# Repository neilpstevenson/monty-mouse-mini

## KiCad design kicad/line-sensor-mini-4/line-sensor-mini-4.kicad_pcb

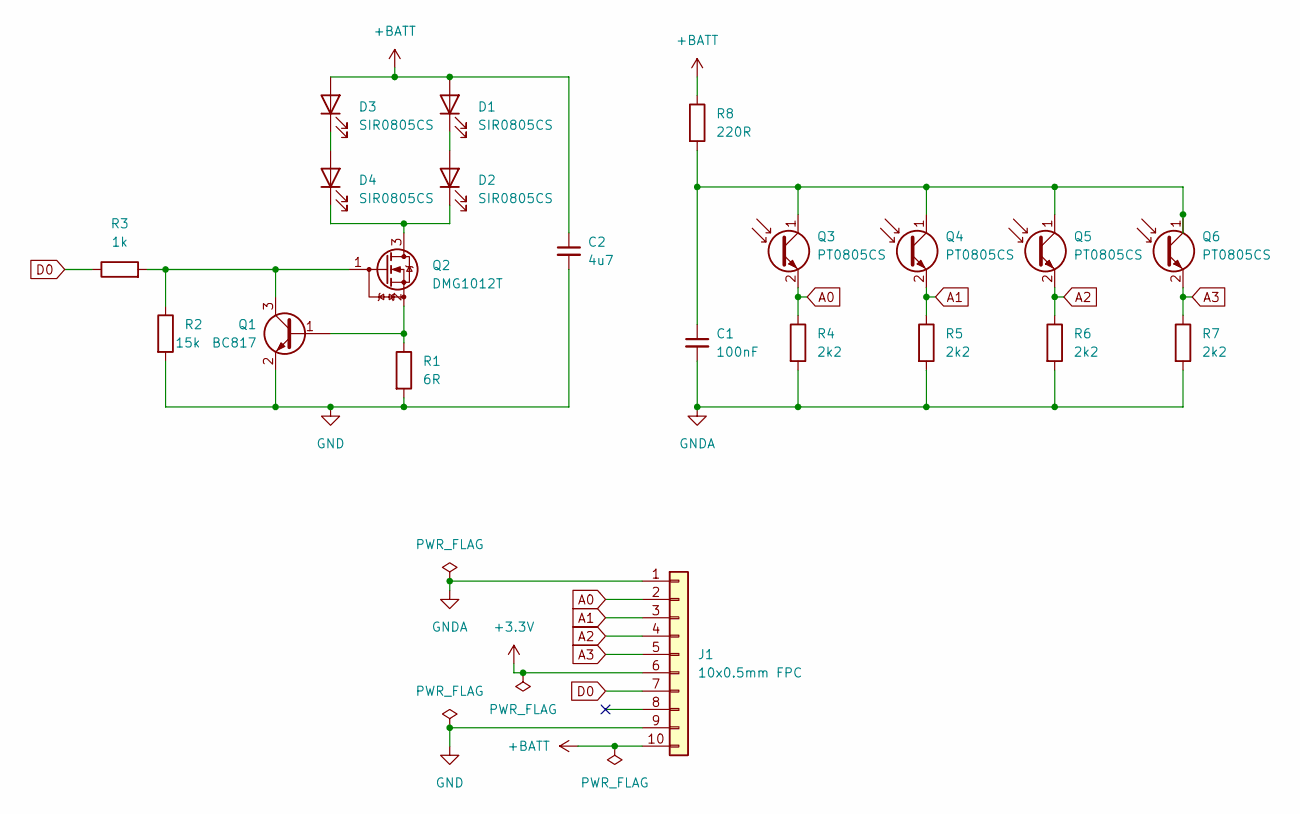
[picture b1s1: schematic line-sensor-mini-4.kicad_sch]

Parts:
C1: 100nF; C_0805_2012Metric
C2: 4u7; C_0805_2012Metric
D1, D2, D3, D4: SIR0805CS; LED_0805_2012Metric_Pad1.15x1.40mm_HandSolder
J1: 10x0.5mm FPC; TE_1-1734839-0_1x10-1MP_P0.5mm_Horizontal
Q1: BC817; SOT-23
Q2: DMG1012T; SOT-323_SC-70
Q3, Q4, Q5, Q6: PT0805CS; LED_0805_2012Metric_Pad1.15x1.40mm_HandSolder
R1: 6R; R_0805_2012Metric
R2: 15k; R_0805_2012Metric
R3: 1k; R_0805_2012Metric
R4, R5, R6, R7: 2k2; R_0805_2012Metric
R8: 220R; R_0805_2012Metric

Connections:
+3.3V: J1.6
+BATT: C2.1, D1.2 (A), D3.2 (A), J1.10, R8.1
A0: J1.2, Q3.2 (E), R4.1
A1: J1.3, Q4.2 (E), R5.1
A2: J1.4, Q5.2 (E), R6.1
A3: J1.5, Q6.2 (E), R7.1
D0: J1.7, R3.1
GND: C2.2, J1.9, Q1.2 (E), R1.2, R2.2
GNDA: C1.2, J1.1, R4.2, R5.2, R6.2, R7.2
unnamed: D1.1 (K), D2.2 (A)
unnamed: D2.1 (K), D4.1 (K), Q2.3 (D)
unnamed: D3.1 (K), D4.2 (A)
unnamed: Q1.1 (B), Q2.2 (S), R1.1
unnamed: Q1.3 (C), Q2.1 (G), R2.1, R3.2
unnamed: C1.1, Q3.1 (C), Q4.1 (C), Q5.1 (C), Q6.1 (C), R8.2

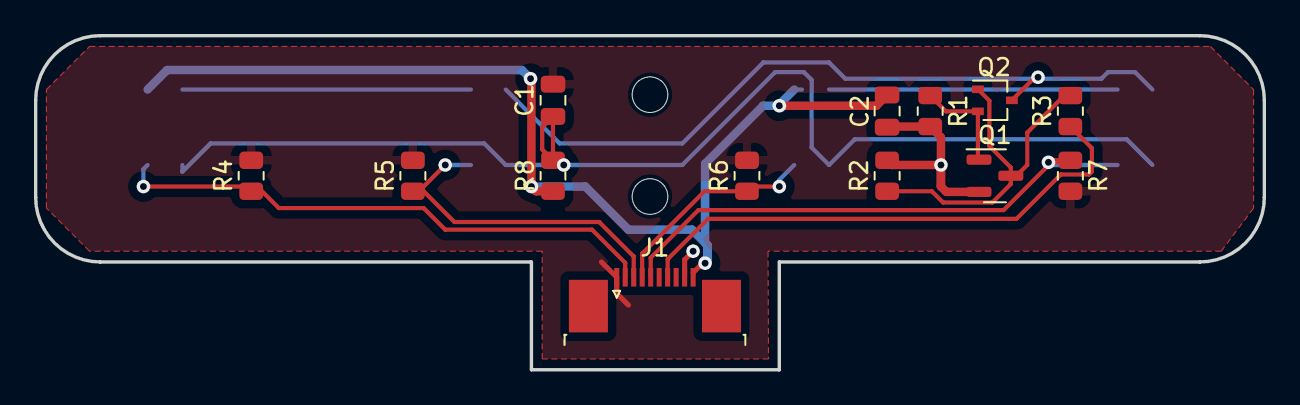
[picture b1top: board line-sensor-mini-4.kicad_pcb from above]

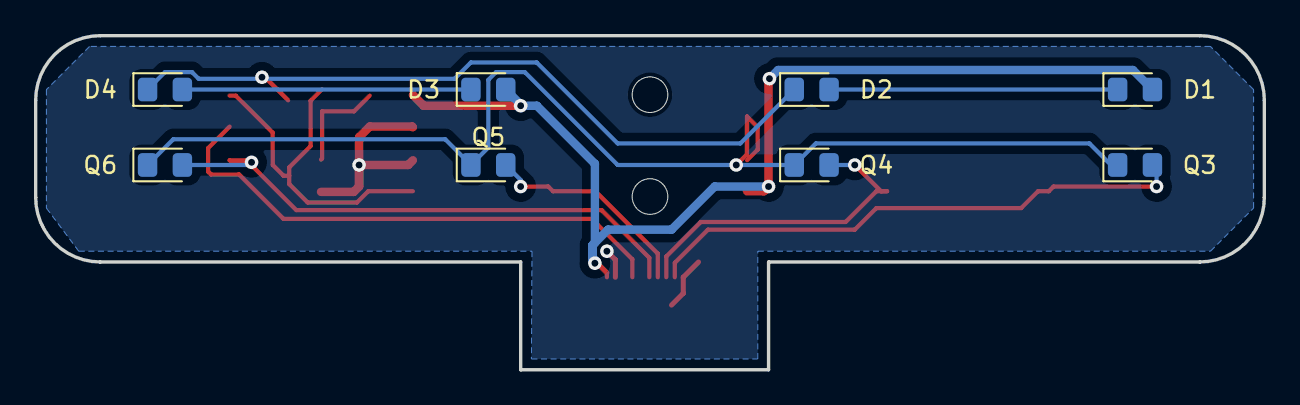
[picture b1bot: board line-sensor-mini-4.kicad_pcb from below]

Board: 2 copper layers, 72.4 x 19.7 mm, 23 parts (8 on the bottom side), 14 nets.

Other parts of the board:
REF-mh: MountingHole_2.1mm
REF-mh#2: MountingHole_2.1mm

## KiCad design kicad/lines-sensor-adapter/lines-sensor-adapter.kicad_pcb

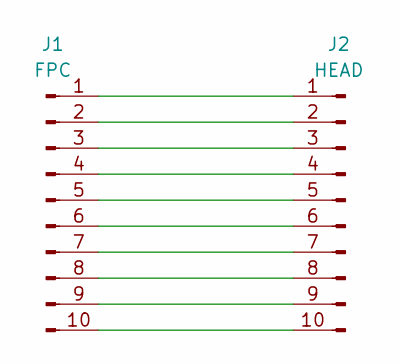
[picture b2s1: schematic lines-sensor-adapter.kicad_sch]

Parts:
J1: FPC; Hirose_FH12-10S-0.5SH_1x10-1MP_P0.50mm_Horizontal
J2: HEAD; PinHeader_1x10_P2.54mm_Vertical

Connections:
unnamed: J1.1, J2.1
unnamed: J1.2, J2.2
unnamed: J1.3, J2.3
unnamed: J1.4, J2.4
unnamed: J1.5, J2.5
unnamed: J1.6, J2.6
unnamed: J1.7, J2.7
unnamed: J1.8, J2.8
unnamed: J1.9, J2.9
unnamed: J1.10, J2.10

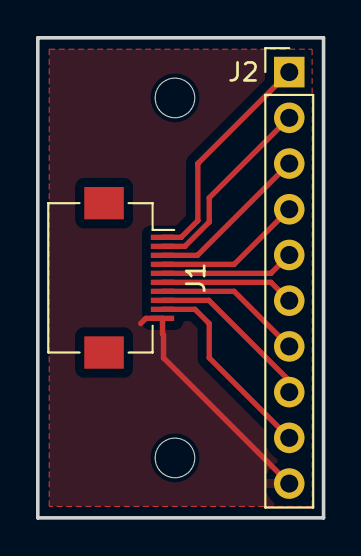
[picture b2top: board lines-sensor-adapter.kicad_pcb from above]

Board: 2 copper layers, 15.9 x 26.7 mm, 4 parts (0 on the bottom side), 10 nets.

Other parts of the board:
REF-mh: MountingHole_2.2mm_M2_DIN965
REF-mh#2: MountingHole_2.2mm_M2_DIN965

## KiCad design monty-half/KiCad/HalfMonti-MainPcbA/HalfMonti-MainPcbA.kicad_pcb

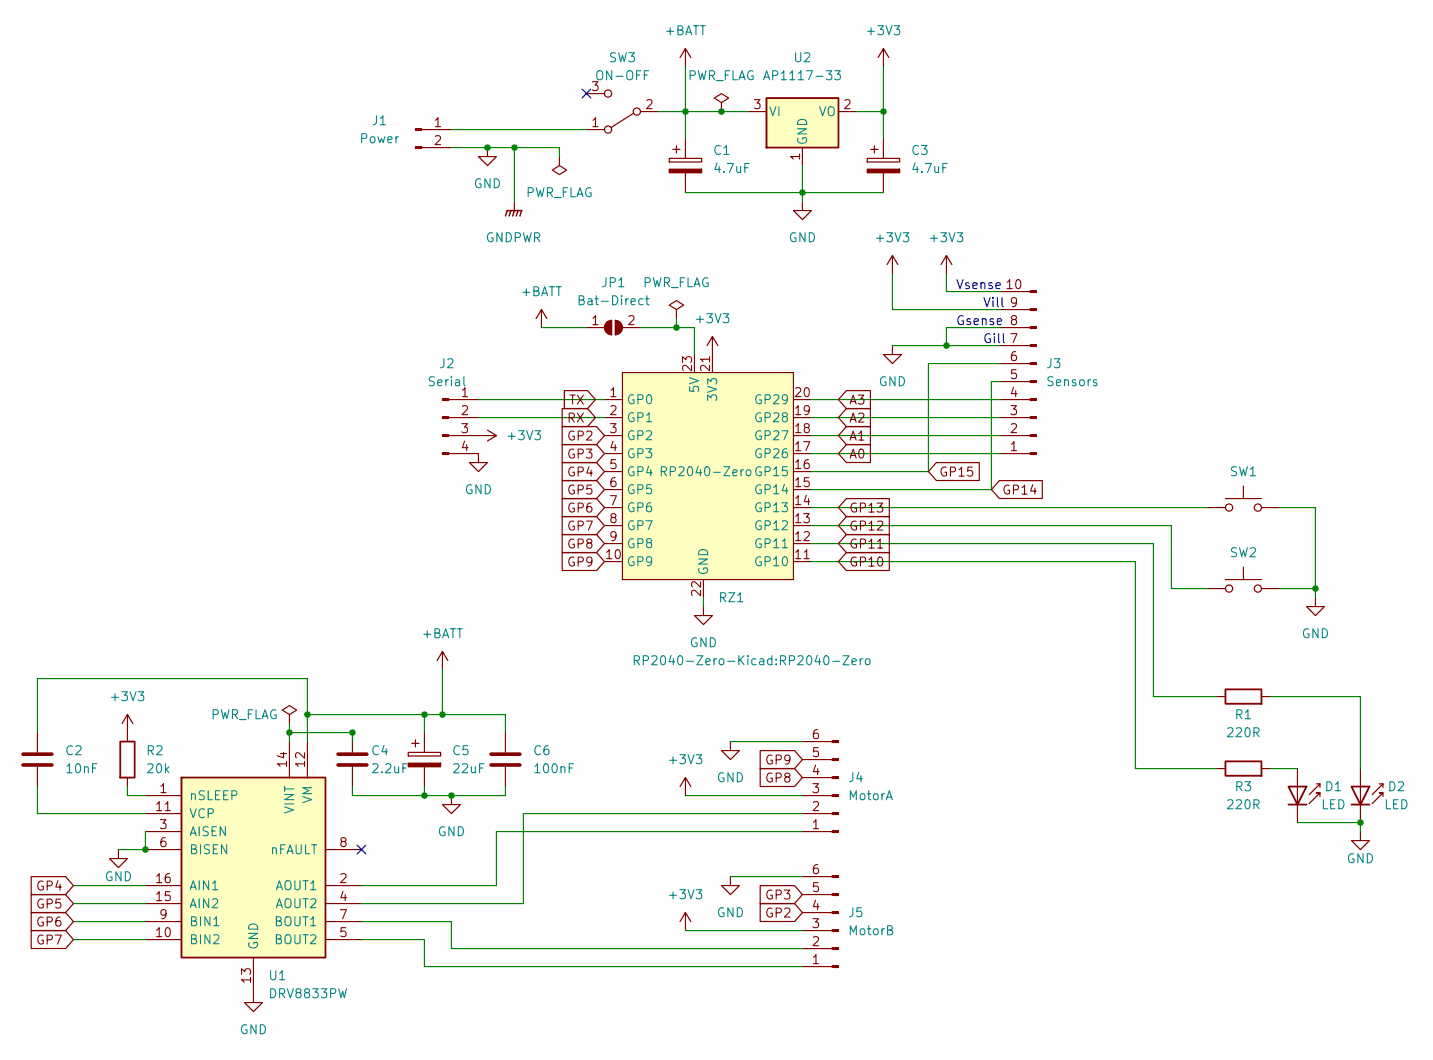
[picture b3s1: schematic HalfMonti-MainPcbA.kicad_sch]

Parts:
C1, C3: 4.7uF; C_0805_2012Metric_Pad1.18x1.45mm_HandSolder
C2: 10nF; C_0805_2012Metric_Pad1.18x1.45mm_HandSolder
C4: 2.2uF; C_0805_2012Metric_Pad1.18x1.45mm_HandSolder
C5: 22uF; CP_Elec_5x3.9
C6: 100nF; C_0805_2012Metric_Pad1.18x1.45mm_HandSolder
D1, D2: LED; LED_1206_3216Metric_Pad1.42x1.75mm_HandSolder
J1: Power; JST_PH_B2B-PH-K_1x02_P2.00mm_Vertical
J2: Serial; PinHeader_1x04_P2.54mm_Vertical
J3: Sensors; PinHeader_1x10_P1.27mm_Vertical
J4: MotorA; PinHeader_1x06_P1.27mm_Vertical
J5: MotorB; PinHeader_1x06_P1.27mm_Vertical
JP1: Bat-Direct; SolderJumper-2_P1.3mm_Open_Pad1.0x1.5mm
R1, R3: 220R; R_0805_2012Metric_Pad1.20x1.40mm_HandSolder
R2: 20k; R_0805_2012Metric_Pad1.20x1.40mm_HandSolder
RZ1: RP2040-Zero
SW1, SW2: SW_Push; SW_SPST_CK_RS282G05A3
SW3: ON-OFF; SW_SPDT_PCM12
U1: DRV8833PW; TSSOP-16_4.4x5mm_P0.65mm
U2: AP1117-33; SOT-223-3_TabPin2

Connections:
+3V3: C3.1, J2.3, J3.9, J3.10, J4.3, J5.3, R2.1, RZ1.21 (3V3), U2.2 (VO)
+BATT: C1.1, C2.1, C5.1, C6.1, JP1.1 (A), SW3.2 (B), U1.12 (VM), U2.3 (VI)
A0: J3.1, RZ1.17 (GP26)
A1: J3.2, RZ1.18 (GP27)
A2: J3.3, RZ1.19 (GP28)
A3: J3.4, RZ1.20 (GP29)
GND: C1.2, C3.2, C4.1, C5.2, C6.2, D1.1 (K), D2.1 (K), J1.2, J2.4, J3.7, J3.8, J4.6, J5.6, RZ1.22 (GND), SW1.2, SW2.2, U1.3 (AISEN), U1.6 (BISEN), U1.13 (GND), U2.1 (GND)
GP2: J5.4, RZ1.3 (GP2)
GP3: J5.5, RZ1.4 (GP3)
GP4: RZ1.5 (GP4), U1.16 (AIN1)
GP5: RZ1.6 (GP5), U1.15 (AIN2)
GP6: RZ1.7 (GP6), U1.9 (BIN1)
GP7: RZ1.8 (GP7), U1.10 (BIN2)
GP8: J4.4, RZ1.9 (GP8)
GP9: J4.5, RZ1.10 (GP9)
GP10: R3.1, RZ1.11 (GP10)
GP11: R1.1, RZ1.12 (GP11)
GP12: RZ1.13 (GP12), SW2.1
GP13: RZ1.14 (GP13), SW1.1
GP14: J3.5, RZ1.15 (GP14)
GP15: J3.6, RZ1.16 (GP15)
unnamed: C2.2, U1.11 (VCP)
unnamed: C4.2, U1.14 (VINT)
unnamed: D1.2 (A), R3.2
unnamed: D2.2 (A), R1.2
unnamed: J1.1, SW3.1 (A)
unnamed: J4.1, U1.2 (AOUT1)
unnamed: J4.2, U1.4 (AOUT2)
unnamed: J5.1, U1.5 (BOUT2)
unnamed: JP1.2 (B), RZ1.23 (5V)
unnamed: R2.2, U1.1 (nSLEEP)
unnamed: J5.2, U1.7 (BOUT1)
RX: J2.2, RZ1.2 (GP1)
TX: J2.1, RZ1.1 (GP0)

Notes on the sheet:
Gsense
Gill
Vsense
Vill

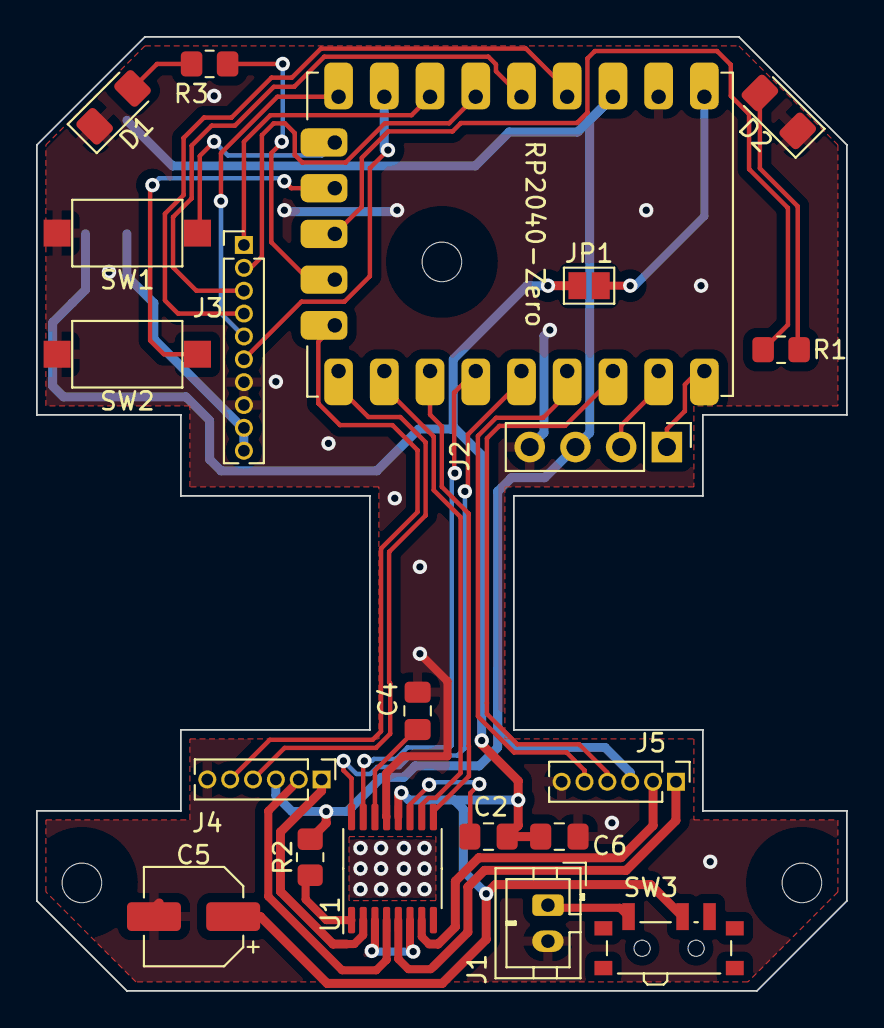
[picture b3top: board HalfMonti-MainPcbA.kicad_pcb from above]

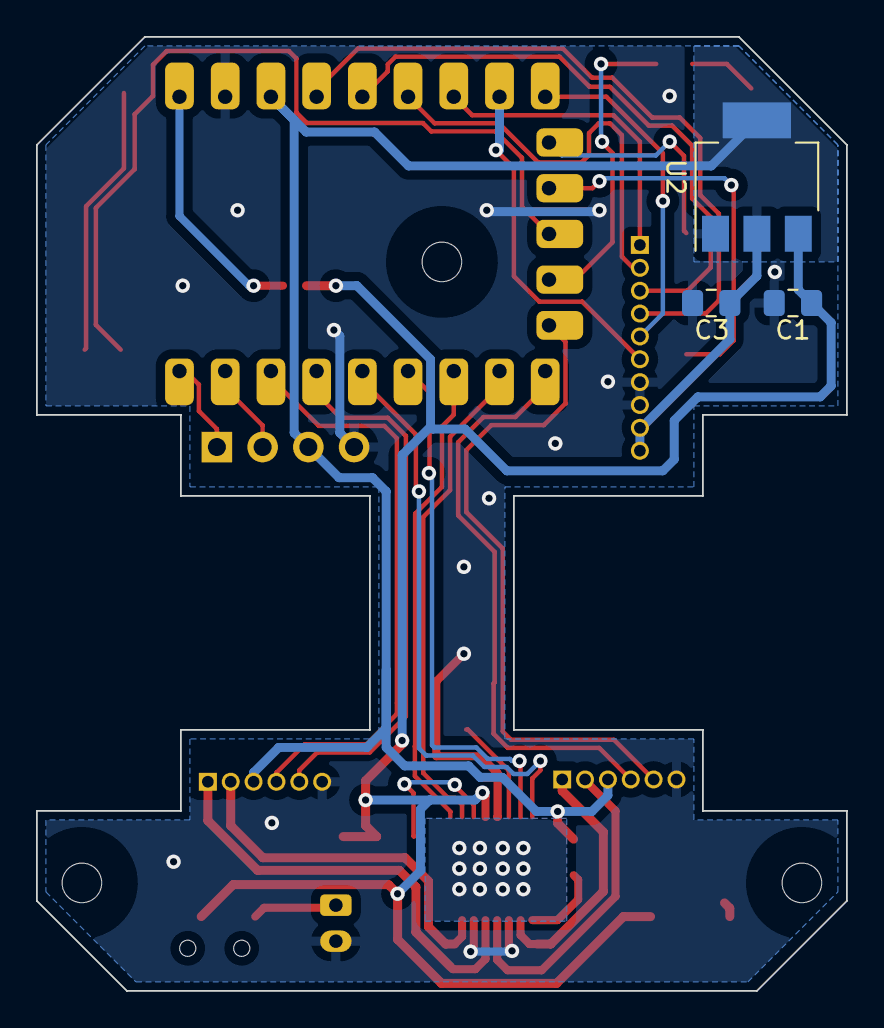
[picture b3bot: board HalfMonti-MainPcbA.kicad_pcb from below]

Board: 2 copper layers, 45.0 x 53.0 mm, 26 parts (4 on the bottom side), 34 nets.

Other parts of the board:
REFH1, REFH2, REFH3: MountingHole_2.2mm_M2

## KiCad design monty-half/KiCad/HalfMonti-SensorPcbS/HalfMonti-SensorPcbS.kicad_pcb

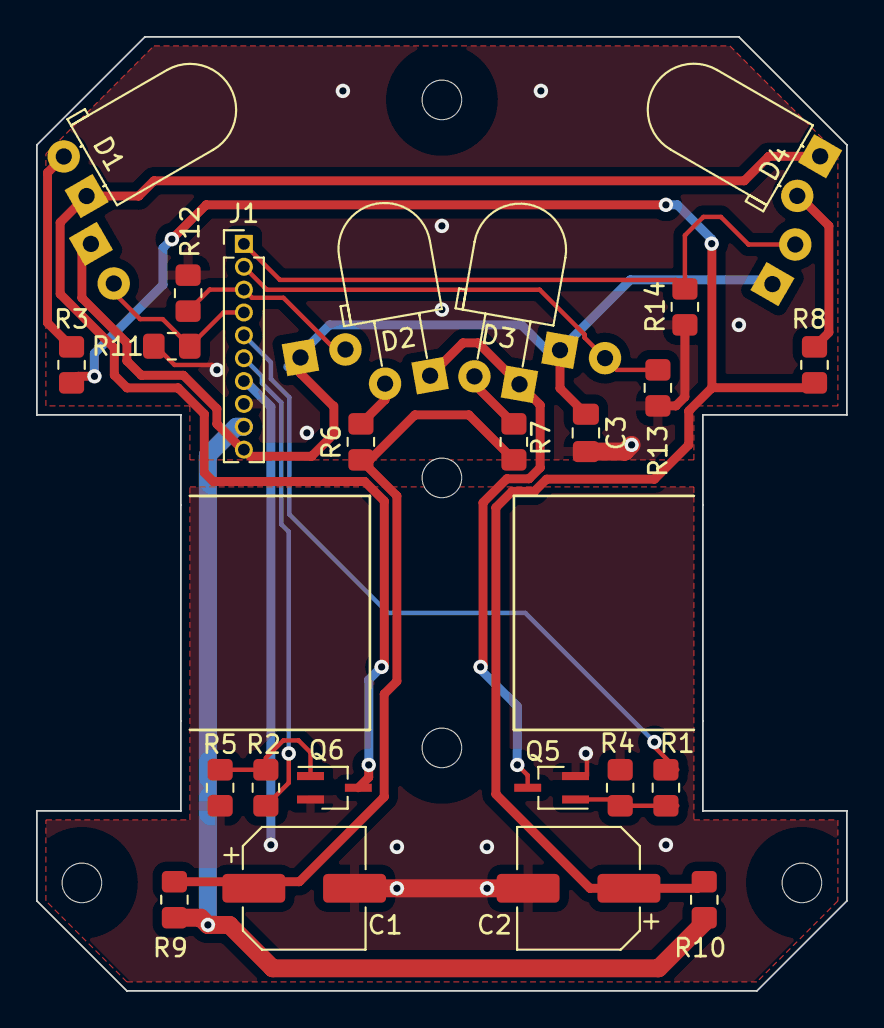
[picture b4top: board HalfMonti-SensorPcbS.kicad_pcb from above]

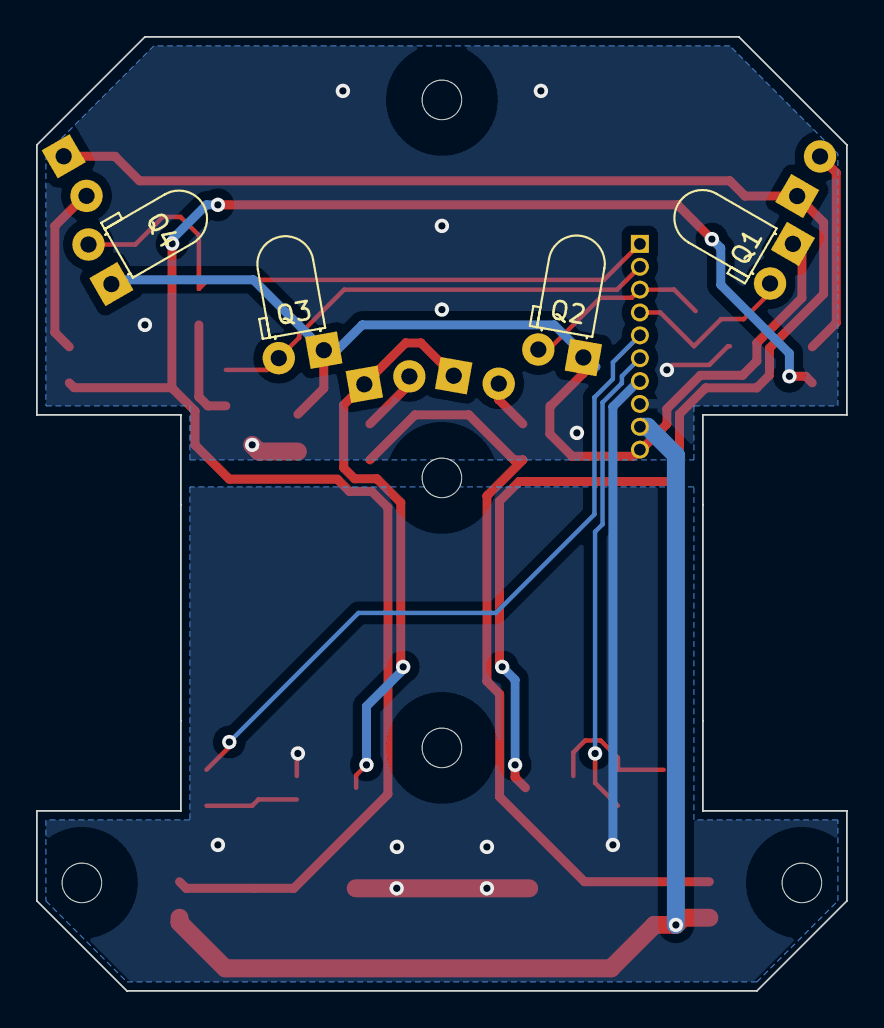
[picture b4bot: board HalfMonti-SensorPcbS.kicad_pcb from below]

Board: 2 copper layers, 45.0 x 53.0 mm, 33 parts (4 on the bottom side), 20 nets.

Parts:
C1, C2: 100uF; CP_Elec_6.3x5.9
C3: 100nF; C_0805_2012Metric_Pad1.18x1.45mm_HandSolder
D1, D2, D3, D4: TLCR5800; LED_D5.0mm_Horizontal_O1.27mm_Z3.0mm
J1: Sensors; PinHeader_1x10_P1.27mm_Vertical
Q1, Q2, Q3, Q4: SFH309; LED_D3.0mm_Horizontal_O1.27mm_Z2.0mm
Q5, Q6: DMG1012T; SOT-323_SC-70_Handsoldering
R1, R2: 1k; R_0805_2012Metric_Pad1.20x1.40mm_HandSolder
R3, R6, R7, R8: 7R2; R_0805_2012Metric_Pad1.20x1.40mm_HandSolder
R4, R5: 10k; R_0805_2012Metric_Pad1.20x1.40mm_HandSolder
R9, R10: 56R; R_0805_2012Metric_Pad1.20x1.40mm_HandSolder
R11, R12, R13, R14: 1.5k; R_0805_2012Metric_Pad1.20x1.40mm_HandSolder
REFH1, REFH1#2, REFH1#3, REFH2, REFH3: MountingHole_2.2mm_M2

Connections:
+3V3: C3.1, J1.10, Q1.1 (C), Q2.1 (C), Q3.1 (C), Q4.1 (C)
A0: J1.1, Q4.2 (E), R14.2
A1: J1.2, Q3.2 (E), R13.2
A2: J1.3, Q2.2 (E), R12.2
A3: J1.4, Q1.2 (E), R11.2
GND: C1.2, C2.2, J1.7, Q5.2 (S), Q6.2 (S), R4.2, R5.2
GNDREF: C3.2, J1.8, R11.1, R12.1, R13.1, R14.1
GP14: J1.5, R1.1
GP15: J1.6, R2.1
unnamed: C1.1, R6.1, R7.1, R9.2
unnamed: C2.1, R3.1, R8.1, R10.2
unnamed: D1.1 (K), D4.1 (K), Q6.3 (D)
unnamed: D1.2 (A), R3.2
unnamed: D2.1 (K), D3.1 (K), Q5.3 (D)
unnamed: D2.2 (A), R6.2
unnamed: D3.2 (A), R7.2
unnamed: D4.2 (A), R8.2
unnamed: Q5.1 (G), R1.2, R4.1
unnamed: Q6.1 (G), R2.2, R5.1
VCC: J1.9, R9.1, R10.1
